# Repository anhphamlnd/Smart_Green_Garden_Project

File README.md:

# Smart_Garden_Project
# 🌱 Smart Garden v2.1 (AVR)
## ĐẶT VẤN ĐỀ
### Khái quát
Trong thời đại công nghệ, việc ứng dụng các hệ thống thông minh sử dụng cảm
biến đang trở thành xu hướng phổ biến. Các cảm biến được tích hợp giúp thu thập dữ
liệu về nhiệt độ, ánh sáng, chuyển động, và nhiều thông tin khác. Từ đó, vườn rau có
thể tự động điều khiển, mang lại sự tiện nghi, an toàn và tiết kiệm năng lượng.
### Lý do chọn đề tài
Việc thiết kế hệ thống vườn thông minh sử dụng các cảm biến là một đề tài có
nhiều tiềm năng ứng dụng trong thực tế. Các lý do chính khiến đề tài này được lựa
chọn bao gồm: Nhu cầu ngày càng tăng về sự tiện lợi, an toàn và tiết kiệm năng lượng
trong quá trình sản xuất; Tiềm năng thị trường lớn cho các giải pháp nông nghiệp
thông minh sử dụng cảm biến có giá thành hợp lý và dễ ứng dụng; Phù hợp với thời
gian nghiên cứu và mục tiêu môn học đề ra.

### 👨‍💻 MCU: ATmega328P  
### 🧠 IDE: CodeVisionAVR  
### 📅 Dự án cuối kỳ — Hệ thống vườn thông minh bán tự động

---

## 📌 Tính năng chính

- 👏 **Điều khiển LED bằng 2 tiếng vỗ tay (KY-037)**
- 🚪 **Mở cổng servo khi phát hiện vật cản (FC-51)**
- 🌡️ **Đo và hiển thị nhiệt độ/độ ẩm bằng DHT11**
- 📟 **Hiển thị thông tin trên màn hình OLED SSD1306**
- 🚨 **Cảnh báo nhiệt độ cao bằng buzzer**
- ⏱️ **Hiển thị thời gian hoạt động hệ thống (uptime)**

---

## ⚙️ Phần cứng sử dụng

| Thiết bị                  | Mô tả                         |
|--------------------------|-------------------------------|
| ATmega328P               | Vi điều khiển chính           |
| DHT11                    | Cảm biến nhiệt độ và độ ẩm    |
| KY-037                   | Cảm biến âm thanh (vỗ tay)    |
| FC-51                    | Cảm biến vật cản hồng ngoại   |
| Servo SG90               | Đóng/mở cổng thông minh       |
| OLED SSD1306 (I2C)       | Hiển thị dữ liệu              |
| Buzzer                   | Cảnh báo nhiệt độ cao         |
| LED                      | Phản hồi khi vỗ tay           |

---

## 🧠 Mô tả chi tiết hoạt động

### 1. 👏 **Vỗ tay bật/tắt đèn**
- Khi phát hiện **2 tiếng vỗ tay liên tiếp**, hệ thống bật/tắt LED.
- Debounce chống nhiễu âm thanh được tích hợp.

### 2. 🚪 **Cảm biến vật cản mở cổng**
- FC-51 phát hiện người/động vật → điều khiển servo mở cửa trong 5 giây → tự đóng.

### 3. 🌡️ **Đo nhiệt độ và cảnh báo**
- Dữ liệu nhiệt độ/độ ẩm được đo mỗi 2 giây.
- Nếu nhiệt độ vượt ngưỡng (mặc định >38°C), buzzer phát cảnh báo chớp nháy.

### 4. 📟 **OLED hiển thị**
- Thông tin được cập nhật:
  - Nhiệt độ
  - Độ ẩm
  - Trạng thái cảnh báo
  - Uptime tính theo `giờ:phút:giây`

---

## 🧾 Sơ đồ kết nối (Pinout)

| Thiết bị     | ATmega328P Pin |
|--------------|----------------|
| KY-037       | PD4 (Digital)  |
| FC-51        | PD5 (Digital)  |
| DHT11        | PD6 (Digital)  |
| Servo        | PD3 (OC2B PWM) |
| OLED (SCL)   | PC5 (A5)       |
| OLED (SDA)   | PC4 (A4)       |
| Buzzer       | PB0 (Digital)  |
| LED          | PB1 (Digital)  |

---
## Chi tiết hoạt động của dự án
### Khi bắt đầu chương trình 
https://github.com/user-attachments/assets/0a29f42b-ba93-440f-8400-c172d5bd55a2

### Khối mở cửa
https://github.com/user-attachments/assets/b30ab63e-868c-456a-b049-d4f57b4c9ab6

### Khối bật tắt đèn khi clap 2 lần 
https://github.com/user-attachments/assets/f04b529f-8dd0-40fd-a486-890ce29304f3

### Cảnh báo khi nhiệt độ > 38 độ C
https://github.com/user-attachments/assets/04ab473f-949c-4921-8430-c594595824e2

## 💻 Cấu trúc chương trình

```c
- main()
  ├── init_all()
  ├── while(1)
       ├── check_clap_switch()
       ├── check_obstacle_sensor()
       ├── check_dht_and_update_display()
       └── update_uptime_display()

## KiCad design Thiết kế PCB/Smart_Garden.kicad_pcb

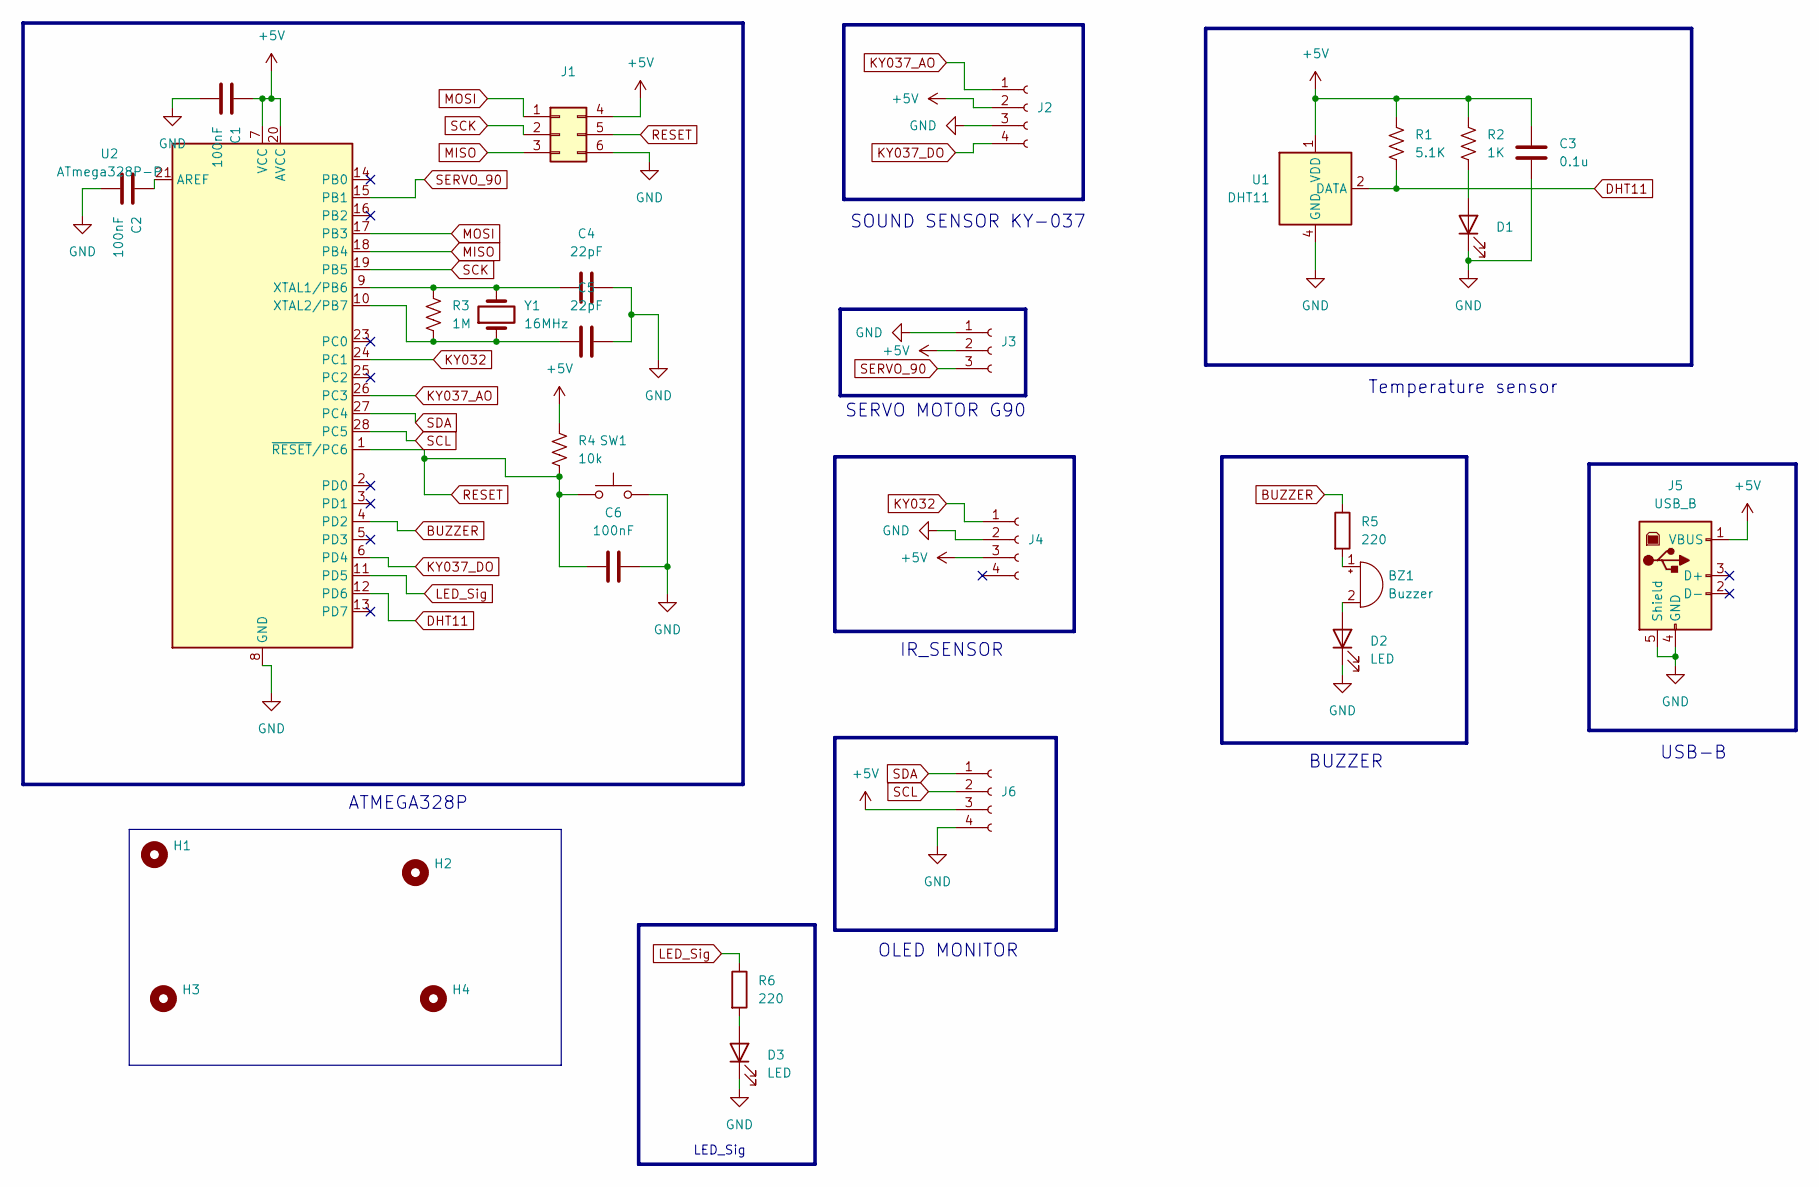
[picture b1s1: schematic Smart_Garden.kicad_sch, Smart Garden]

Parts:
BZ1: Buzzer; Buzzer_12x9.5RM7.6
C1, C2, C6: 100nF; CP_Radial_D4.0mm_P1.50mm
C3: 0.1u; CP_Radial_D4.0mm_P1.50mm
C4, C5: 22pF; CP_Radial_D4.0mm_P1.50mm
D1, D2, D3: LED; LED_D4.0mm
H1, H2, H3, H4: MountingHole; MountingHole_3.2mm_M3_DIN965
J1: Conn_02x03_Top_Bottom; PinSocket_2x03_P2.54mm_Vertical
J2, J4, J6: Conn_01x04_Socket; PinSocket_1x04_P2.54mm_Vertical
J3: Conn_01x03_Socket; PinSocket_1x03_P2.54mm_Vertical
J5: USB_B; USB_B_Lumberg_2411_02_Horizontal
R1: 5.1K; R_Axial_DIN0309_L9.0mm_D3.2mm_P12.70mm_Horizontal
R2: 1K; R_Axial_DIN0309_L9.0mm_D3.2mm_P12.70mm_Horizontal
R3: 1M; R_Axial_DIN0309_L9.0mm_D3.2mm_P12.70mm_Horizontal
R4: 10k; R_Axial_DIN0309_L9.0mm_D3.2mm_P12.70mm_Horizontal
R5, R6: 220; R_Axial_DIN0309_L9.0mm_D3.2mm_P12.70mm_Horizontal
SW1: SW_Push; SW_PUSH-12mm
U1: DHT11; Aosong_DHT11_5.5x12.0_P2.54mm
U2: ATmega328P-P; DIP-28_W7.62mm_Socket
Y1: 16MHz; Crystal_HC49-U_Vertical

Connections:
+5V: C1.2, C3.1, J1.4, J2.2, J3.2, J4.3, J5.1 (VBUS), J6.3, R1.1, R2.1, R4.2, U1.1 (VDD), U2.7 (VCC), U2.20 (AVCC)
BUZZER: R5.1, U2.4 (PD2)
DHT11: R1.2, U1.2 (DATA), U2.12 (PD6)
GND: C1.1, C2.1, C3.2, C4.2, C5.2, C6.2, D1.1 (K), D2.1 (K), D3.1 (K), J1.6, J2.3, J3.1, J4.2, J5.4 (GND), J5.5 (Shield), J6.4, SW1.2, U1.4 (GND), U2.8 (GND), U2.22 (GND)
KY032: J4.1, U2.24 (PC1)
KY037_AO: J2.1, U2.26 (PC3)
KY037_DO: J2.4, U2.6 (PD4)
LED_Sig: R6.1, U2.11 (PD5)
MISO: J1.3, U2.18 (PB4)
MOSI: J1.1, U2.17 (PB3)
unnamed: BZ1.1 (+), R5.2
unnamed: BZ1.2 (-), D2.2 (A)
unnamed: D1.2 (A), R2.2
unnamed: D3.2 (A), R6.2
unnamed: C2.2, U2.21 (AREF)
unnamed: C4.1, R3.1, U2.9 (XTAL1/PB6), Y1.2
unnamed: C5.1, R3.2, U2.10 (XTAL2/PB7), Y1.1
RESET: C6.1, J1.5, R4.1, SW1.1, U2.1 (~RESET/PC6)
SCK: J1.2, U2.19 (PB5)
SCL: J6.2, U2.28 (PC5)
SDA: J6.1, U2.27 (PC4)
SERVO_90: J3.3, U2.15 (PB1)

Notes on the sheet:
ATMEGA328P
OLED MONITOR
BUZZER
Temperature sensor
LED_Sig
IR_SENSOR
SOUND SENSOR KY-037
USB-B
SERVO MOTOR G90

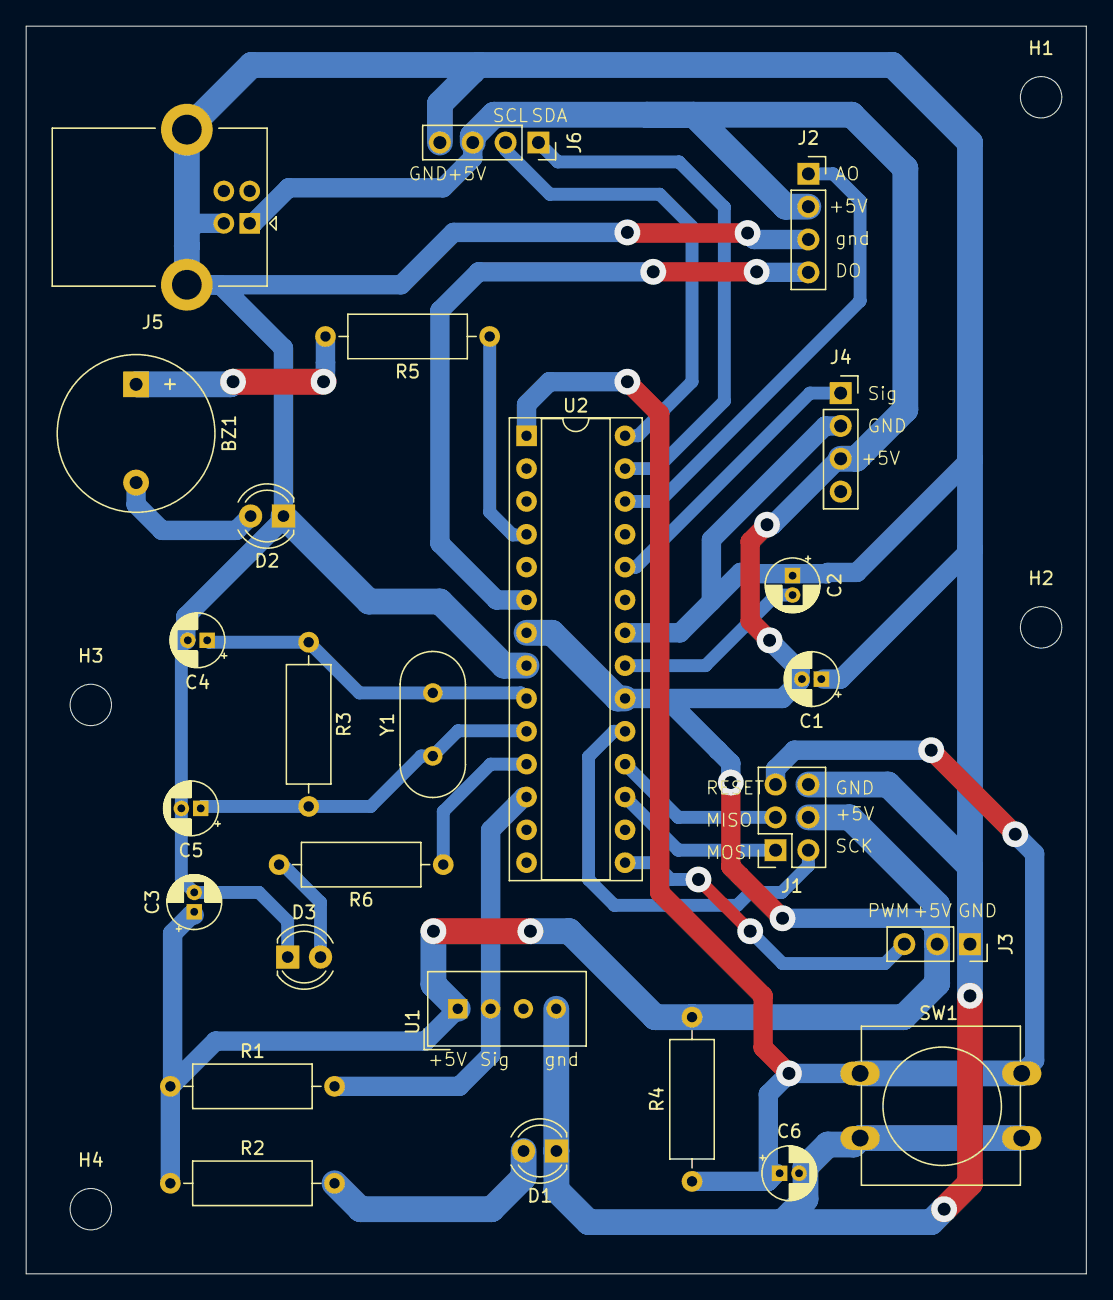
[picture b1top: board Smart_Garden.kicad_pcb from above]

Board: 2 copper layers, 82.0 x 96.5 mm, 30 parts (0 on the bottom side), 22 nets.

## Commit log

2025-05-27 Update PCB and simulation
2025-05-27 update algorithm flowchart
2025-05-28 fix comment in code
2025-05-28 update name
2025-05-29 fix timer
